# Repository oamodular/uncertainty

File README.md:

# *Uncertainty is now OSHW! both the software and the hardware!*

This readme needs to be updated to reflect this and to talk about the many other languages that people have used to create new firmware for Uncertainty. Right now I just want to say that the 4hp DIY version of Uncertainty is still a work in progress. It's been built, but we're in the process of trying to figure out why it doesn't work. The 2hp SMT version of Uncertainty is the one that we sell [here](https://oamodular.org/products/uncertainty).

What remains below is the previous readme. It contains the pinout for Uncertainty's Seeeduino Xiao RP2040 and some example Python code…

# Hack Uncertainty for fun and profit

Uncertainty's firmware is open-source and easy to swap with a humble USB-C cable. You can write your own firmware in C++, MicroPython, CircuitPython, and probably a bunch of other languages. It's startlingly easy to work and this document will outline the whole deal. Let's go…

## Uncertainty’s Heart

We’re working with the mighty RP2040, a dual-core 133 MHz arm processor that is just a silly amount of power for outputting gates. Heck, you can easily overclock to over 300 MHz. Really hoping people make some messed up things.

## Uncertainty’s I/O

- one CV input that can recognize signals -5v to +5v (resolution is functionally close to 10-bit, so there probably isn’t quite the precision for v/oct)
- eight +5v gate outputs that each have their own LED (if you turn on the gate, you turn on the LED; they can’t be decoupled)
- a three pin I2C connector (this feature is experimental and largely untested)

To access this I/O use the following pins. You can use other pins, but they won’t work. I don’t know why you’d use other pins. Use these pins:

|        | Pin # |
| ------ | ------ |
|CV input|26|
|Gate 1|27|
|Gate 2|28|
|Gate 3|29|
|Gate 4|0|
|Gate 5|3|
|Gate 6|4|
|Gate 7|2|
|Gate 8|1|
|I2C SDA|6|
|I2C SCL|7|

## How to reinstall the default firmware

You hold down the boot button when you plug in the USB-C as described in the *Getting started* section. Then you drag ```uncertainty.uf2``` onto the RPI-RP2 disk. It should then unmount. All set! The same works for any .uf2 firmware.

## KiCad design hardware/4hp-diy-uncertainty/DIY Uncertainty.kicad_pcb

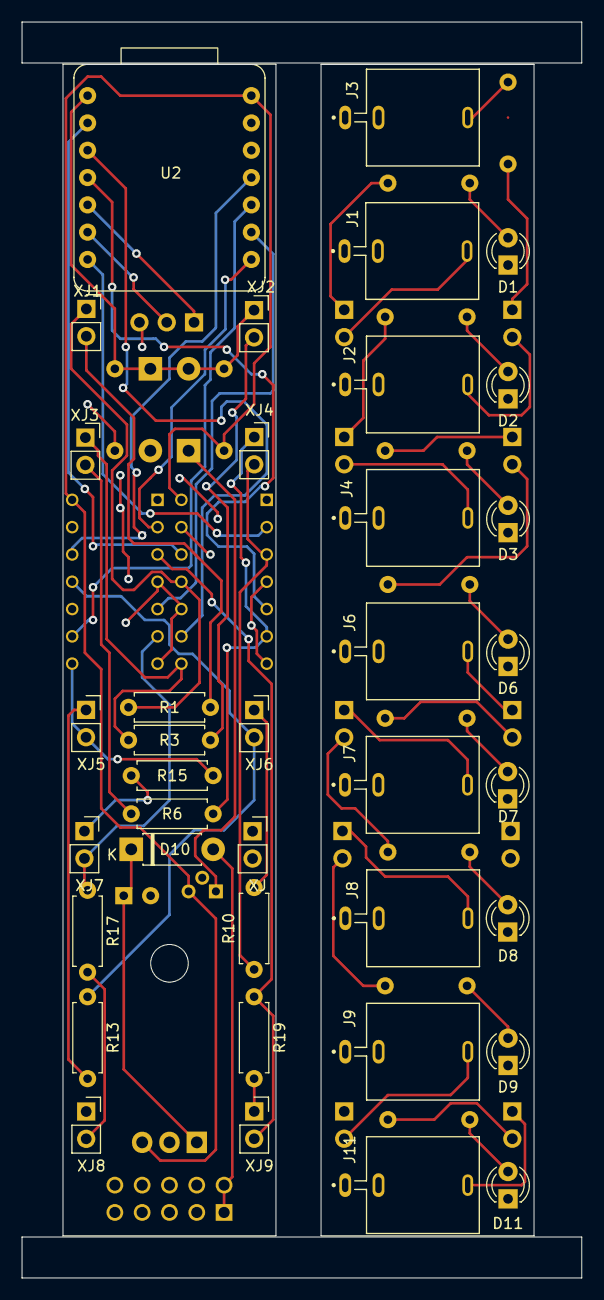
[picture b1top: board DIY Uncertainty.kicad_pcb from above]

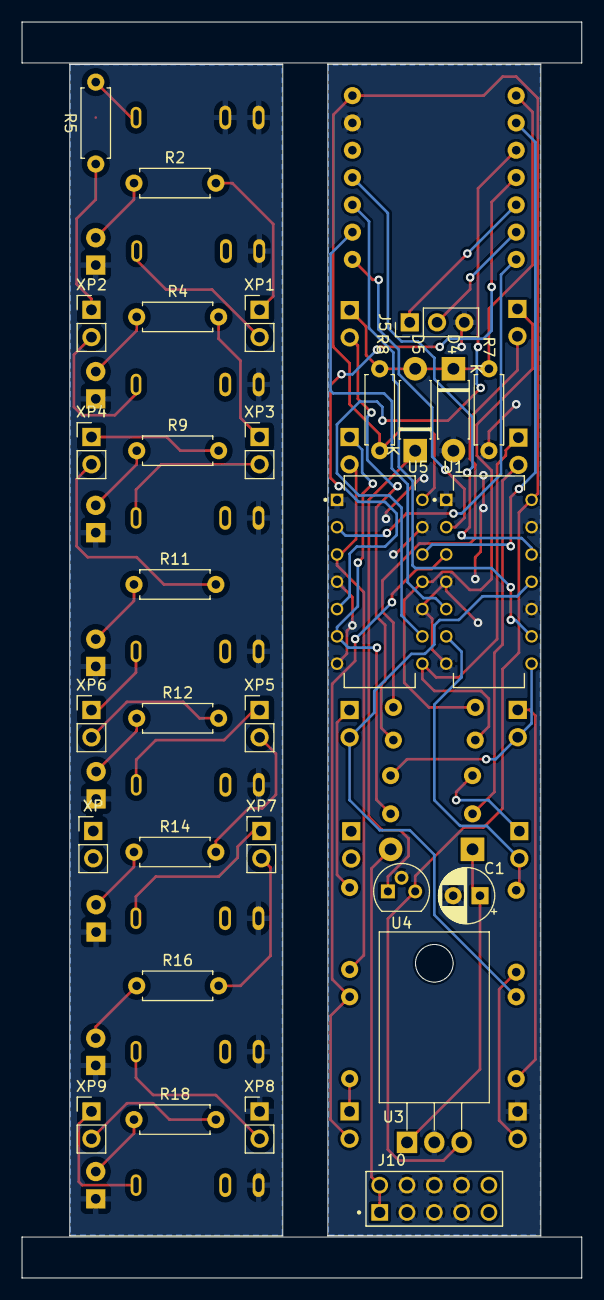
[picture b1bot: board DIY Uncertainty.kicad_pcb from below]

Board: 2 copper layers, 52.1 x 116.8 mm, 67 parts (30 on the bottom side), 41 nets.

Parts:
C1: 22uF; CP_Radial_D5.0mm_P2.50mm
D1, D2, D3, D6, D7, D8, D9, D11: LED; LED-THT Red Angle130-L-47XEC
D4, D5, D10: 1N5819; D_DO-41_SOD81_P7.62mm_Horizontal
J1, J2, J3, J4, J6, J7, J8, J9, J11: AudioJack2; Socket-3.5mm THT-Thonkiconn PJ398SM-12
J5: Conn_01x03_Pin; PinHeader_1x03_P2.54mm_Vertical
J10: Connector-2x5 2.54p THT-861400102YO9323LF
R1, R3, R6, R10, R13, R15, R17, R19: 1K; R_Axial_DIN0207_L6.3mm_D2.5mm_P7.62mm_Horizontal
R2, R4, R9, R11, R12, R14, R16, R18: 300; R_Axial_DIN0207_L6.3mm_D2.5mm_P7.62mm_Horizontal
R5, R7, R8: 100K; R_Axial_DIN0207_L6.3mm_D2.5mm_P7.62mm_Horizontal
U1, U5: SN74HCT125DE4; Quad Bus-Tri-State Quad Bus non-inverting THT-SN74HCT125NE4
U2: SeeeduinoXIAO; Microcontroller-XIAO RP2040
U3: L7805CV; TO-220-3_Horizontal_TabDown
U4: L78L33ACZTR; TO-92
XJ, XJ1, XJ2, XJ3, XJ4, XJ5, XJ6, XJ7, XJ8, XJ9: PinSocket_1x02_P2.54mm_Vertical
XP, XP1, XP2, XP3, XP4, XP5, XP6, XP7, XP8, XP9: PinHeader_1x02_P2.54mm_Vertical

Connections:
+3.3V: D5.1 (K), U4.1 (VO)
+5V: R8.2, U1.14 (VCC), U2.14 (5V), U3.3 (VO), U4.3 (VI), U5.14 (VCC)
+12V: D10.2 (A), J10.01 (Pin_1), J10.02 (Pin_2)
GND: C1.2, D1.1 (K), D2.1 (K), D3.1 (K), D4.2 (A), D6.1 (K), D7.1 (K), D8.1 (K), D9.1 (K), D11.1 (K), J1.1, J2.1, J3.1, J3.2, J4.1, J5.3, J6.1, J7.1, J8.1, J9.1, J10.03 (Pin_3), J10.04 (Pin_4), J10.05 (Pin_5), J10.06 (Pin_6), J10.07 (Pin_7), J10.08 (Pin_8), J11.1, R7.1, U1.1 (1~OE), U1.4 (2~OE), U1.7 (GND), U1.10 (3~OE), U1.13 (4~OE), U2.13 (GND), U3.2 (GND), U4.2 (GND), U5.1 (1~OE), U5.4 (2~OE), U5.7 (GND), U5.10 (3~OE), U5.13 (4~OE), XJ8.1, XP8.1
unnamed: D1.2 (A), R2.1
unnamed: D2.2 (A), R4.1
unnamed: D3.2 (A), R9.1
unnamed: D4.1 (K), D5.2 (A), R5.1, R7.2, R8.1, U2.1 (PA02_A0_D0), XJ2.1, XP2.1
unnamed: D6.2 (A), R11.1
unnamed: D7.2 (A), R12.1
unnamed: D8.2 (A), R14.1
unnamed: D9.2 (A), R16.1
unnamed: C1.1, D10.1 (K), U3.1 (VI)
unnamed: D11.2 (A), R18.1
unnamed: J1.3, R1.2, XJ1.2, XP1.2
unnamed: J2.3, R3.2, XJ2.2, XP2.2
unnamed: J3.3, R5.2
unnamed: J4.3, R6.2, XJ3.2, XP3.2
unnamed: J5.1, U2.5 (PA8_A4_D4_SDA)
unnamed: J5.2, U2.6 (PA9_A5_D5_SCL)
unnamed: J6.3, R10.2, XJ6.1, XP6.1
unnamed: J7.3, R13.2, XJ5.1, XP5.1
unnamed: J8.3, R15.2, XJ7.1, XP7.1
unnamed: J9.3, R17.2, XJ8.2, XP8.2
unnamed: J11.3, R19.2, XJ9.1, XP9.1
unnamed: U1.2 (1A), U2.8 (PB09_A7_D7_RX)
unnamed: R18.2, R19.1, U1.3 (1Y), XJ9.2, XP9.2
unnamed: U1.5 (2A), U2.9 (PA7_A8_D8_SCK)
unnamed: R16.2, R17.1, U1.6 (2Y), XJ7.2, XP7.2
unnamed: U1.9 (3A), U2.10 (PA5_A9_D9_MISO)
unnamed: R14.2, R15.1, U1.8 (3Y), XJ5.2, XP5.2
unnamed: U1.12 (4A), U2.11 (PA6_A10_D10_MOSI)
unnamed: R12.2, R13.1, U1.11 (4Y), XJ6.2, XP6.2
unnamed: U2.2 (PA4_A1_D1), U5.12 (4A)
unnamed: U2.3 (PA10_A2_D2), U5.9 (3A)
unnamed: U2.4 (PA11_A3_D3), U5.5 (2A)
unnamed: U2.7 (PB08_A6_D6_TX), U5.2 (1A)
unnamed: R10.1, R11.2, U5.3 (1Y), XJ4.2, XP4.2
unnamed: R6.1, R9.2, U5.6 (2Y), XJ4.1, XP4.1
unnamed: R3.1, R4.2, U5.8 (3Y), XJ3.1, XP3.1
unnamed: R1.1, R2.2, U5.11 (4Y), XJ1.1, XP1.1

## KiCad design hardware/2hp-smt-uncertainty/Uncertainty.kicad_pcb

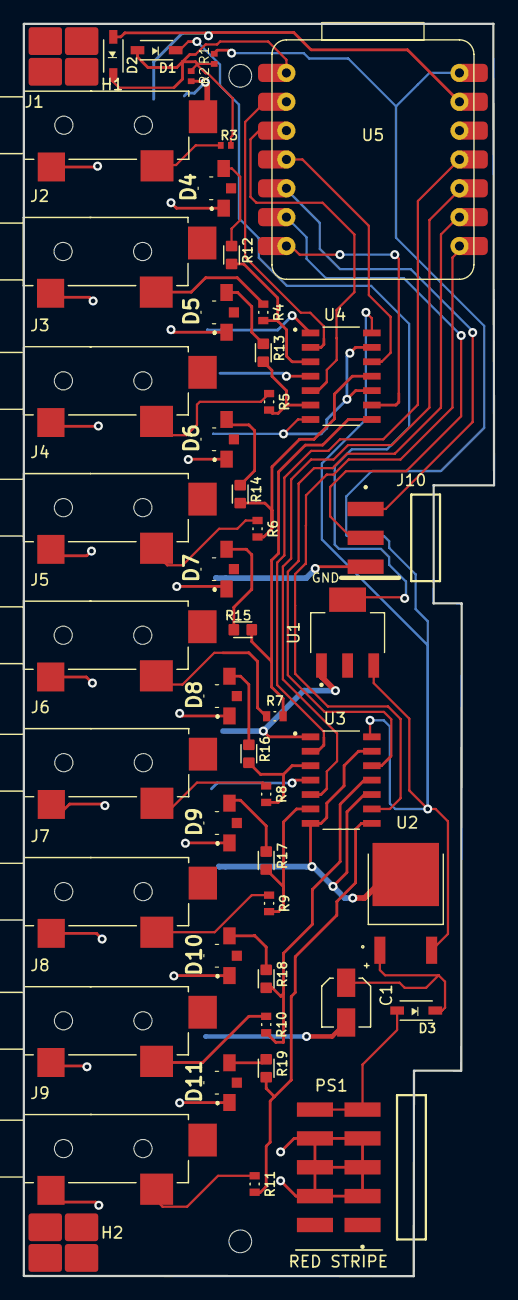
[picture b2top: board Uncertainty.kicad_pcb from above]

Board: 2 copper layers, 41.4 x 110.3 mm, 49 parts (0 on the bottom side), 4 nets.

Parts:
C1: CAP_EEE-FT1E220AR
D1, D2, D3: SOD3715X145N; Diode-1N5819HW-7-F
D4, D5, D6, D7, D8, D9, D10, D11: APPA3010SURCK; LED-SMD Red SideEmit Angle30 3x1mm -APPA3010SURCK
H1, H2: Wurth 7466303; Hardware-Right angle SMT mounting block-Wurth 7466303
J1, J2, J3, J4, J5, J6, J7, J8, J9: SWITCHCRAFT_35RASMT2AHNTRX
J10: SAMTEC_TSM-103-01-L-SH
PS1: SAMTEC_TSM-105-01-L-DH
R1, R2, R3: In Resist-ERJ-2RKF1003X
R4, R5, R6, R7, R8, R9, R10, R11: Out Resist-RES_ERJPA3D1001V
R12, R13, R14, R15, R16, R17, R18, R19: RESC1608X50N
U1: VREG_LM1117IMPX-3.3/NOPB; VREG_LM1117IMPX-3.3_NOPB
U2: VREG_L7805CDT-TR
U3, U4: SN74HCS125QDRQ1; Quad Bus-SMD SN74HCS125QDRQ1
U5: XIAO-RP2040

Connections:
3.3V: D1.C, U1.4
5V: R1.2, U1.3, U2.2, U3.14, U4.14, U5.14
Ground: C1.2, D2.A, D4.1, D5.1, D6.1, D7.1, D8.1, D9.1, D10.1, D11.1, J1.3, J1.5, J2.5, J3.5, J4.5, J5.5, J6.5, J7.5, J8.5, J9.5, J10.03, PS1.03, PS1.04, PS1.05, PS1.06, PS1.07, PS1.08, R2.2, U1.1, U2.3, U3.1, U3.4, U3.7, U3.10, U3.13, U4.1, U4.4, U4.7, U4.10, U4.13, U5.13
Power: C1.1, D3.A, D3.C, PS1.09, PS1.10, U1.2, U2.1

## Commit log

2022-12-25 Readme fix
2022-12-25 Adding uncertainty source
2022-12-25 Adding uncertainty binary
2022-12-25 Adding example firmware, the gate selector
2022-12-25 Seeeduino Xiao RP2040 image for the readme
2022-12-25 Adding image to readme and fixing a typo
2022-12-26 Add LICENSE
2022-12-26 Fixed some bugs. Made it so 0v is gate 1 and moving to higher (or lower!) voltage moves to a higher gate.
2023-02-10 Adding various Uncertainty firmwares. Some are unfinished. Some are barely started. Some work quite well. All need some cleanup and commenting.
2023-02-12 cleaning up the repo
2023-02-12 moving the current stable uncertainty
2023-02-14 Making the digital schmidt trigger threshold voltages assymetrical to deal with floating inputs without leaving all LEDs on.
2023-02-22 Fixing some weird edge cases where Uncertainty might get temporarily stuck in a weird state.
2023-02-24 Demo burst firmware.
2023-02-24 PUtting the startup sequence in its own cute lil function.
2023-03-03 Tweaking and polishing VU code heavily.
2023-03-03 Adding DC offset filter to input.
2023-03-03 Removing extra binaries.
2023-03-07 Adding options for jumping i2c pins together to enable "max amplitude only" mode or to flip the meter display.
2023-03-07 Output raw, scaled analog in as midi cc 1 on channel 1
2023-03-12 moving vu meter firmware into stable
2023-04-14 Adding continuous burst.
2023-04-14 Adding burst binary
2023-06-10 adding uncertainty hardware and license
2023-06-10 Updated README.md to mention that's it's OSHW!
2023-06-26 Adding i2c follower (works) and i2c leader (currently broken)
2023-06-26 Adding LFO, oscillator commands. Audio interrupt is screwing up i2c, need to move to another core.
2023-06-26 So many tweaks. Just so much. Everything work now. Audio rate. Can't believe it. Very happy. I think I need a bath.
2023-06-27 Now 3 params to VCO lets you set note, middle-C freq, and number of divisons in an octave.
2023-06-27 Committing binary.
2023-06-27 Removing bad binary
2023-08-05 misc updates from kate
2023-08-05 renaming
2023-08-05 ignore kicad cache folders
2024-02-02 a bom
    so people can actually build this thing
2024-04-10 Redoing the directory structure
2024-04-11 Adding CircuitPython code and some documenation
2024-04-11 Adding a note that this code is just a placeholder
2024-04-11 Improving the docs
2024-04-28 uncertainty.py works
2024-04-28 tweak to coin flip logic
2024-05-01 adding a .uf2 for easy installation
2024-06-03 tweaked the values for gate thresholds in uncertainty.py and updated the .uf2
2024-06-23 adding a little library for working with uncertainty
2024-06-25 walking script, inspired by david
2026-01-15 Initializing state to all 1s.
